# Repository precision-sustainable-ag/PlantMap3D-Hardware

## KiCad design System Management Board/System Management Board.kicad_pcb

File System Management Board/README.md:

The system management board handles all power distribution in the multi-camera system and a few other auxiliary functions. The PCB is designed using KiCad.

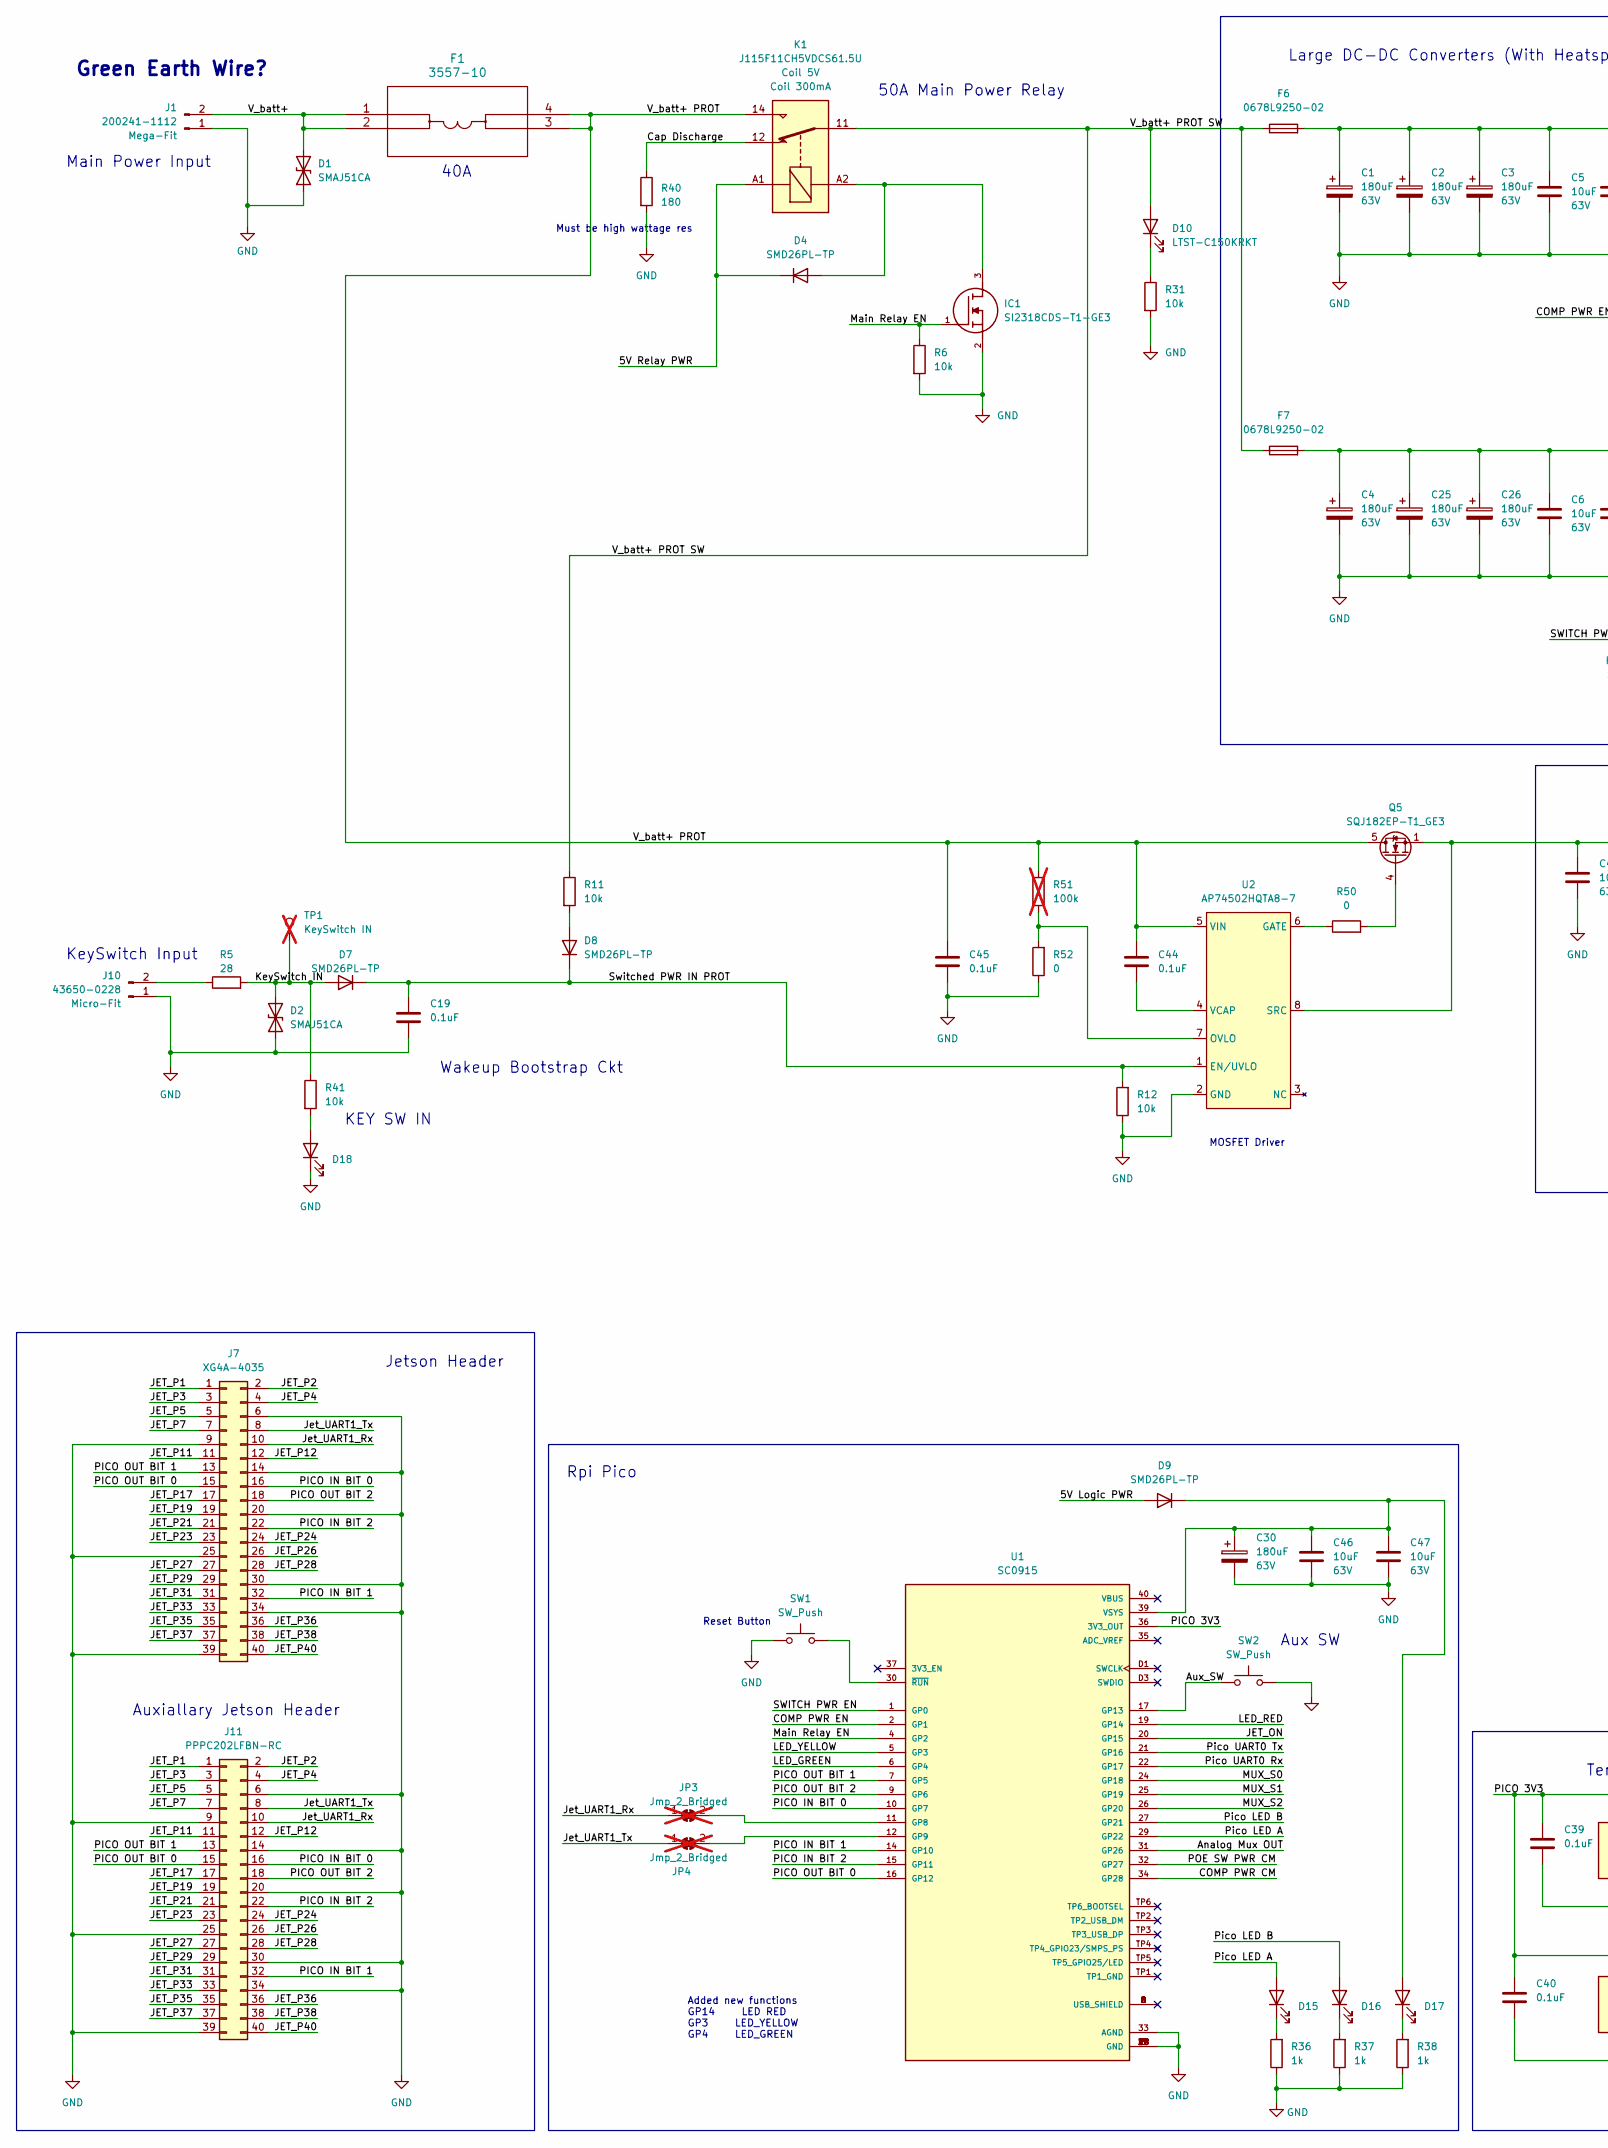
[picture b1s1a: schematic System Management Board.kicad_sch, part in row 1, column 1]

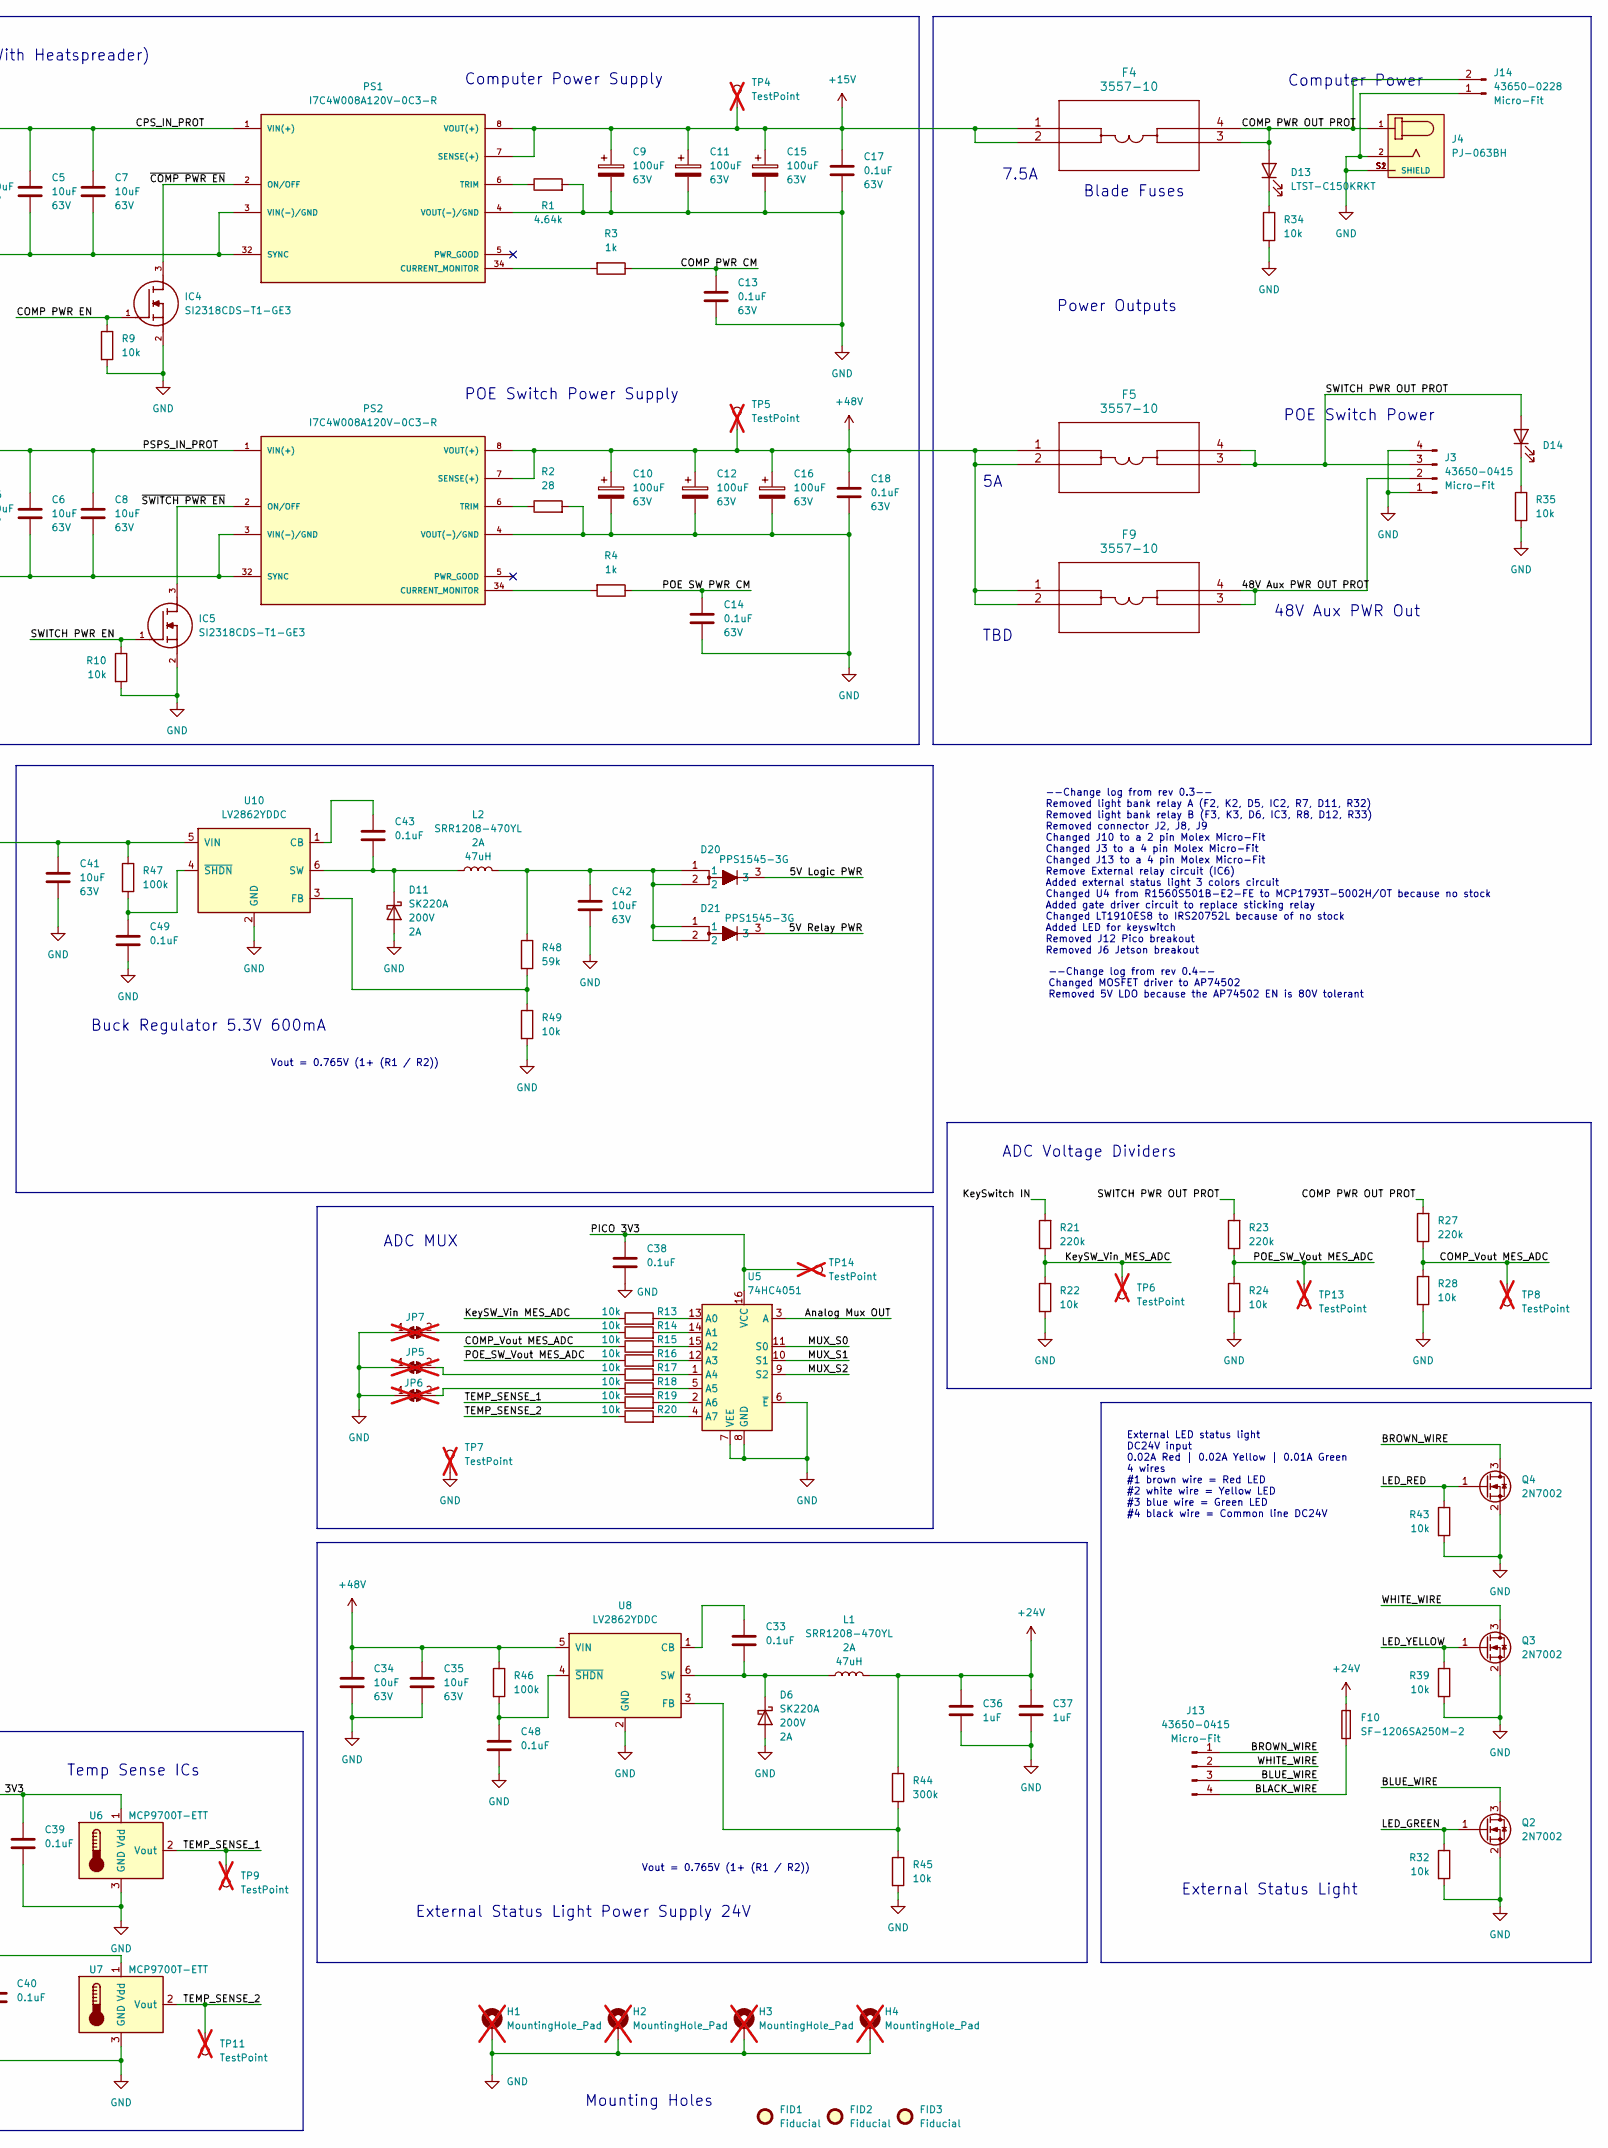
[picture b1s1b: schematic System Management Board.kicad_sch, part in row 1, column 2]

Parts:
C1, C2, C3, C4, C25, C26, C30: 180uF; CP_Elec_10x12.6; Voltage 63V
C5, C6, C7, C8, C34, C35, C41, C42, C46, C47: 10uF; C_1210_3225Metric; Voltage 63V
C9, C10, C11, C12, C15, C16: 100uF; CP_Elec_10x12.6; Voltage 63V
C13, C14, C17, C18, C19, C33, C38, C39, C40, C43, C44, C45, C48, C49: 0.1uF; C_0603_1608Metric; Voltage 63V
C36, C37: 1uF; C_1210_3225Metric
D1, D2: SMAJ51CA; D_SMA
D4, D7, D8, D9: SMD26PL-TP; D_SOD-123F
D6, D11: SK220A; D_SMA; Voltage 200V
D10, D13, D14, D15, D16, D17, D18: LTST-C150KRKT; LED_1206_3216Metric
D20, D21: PPS1545-3G; TO-277B
F1, F4, F5, F9: 3557-10
F6, F7: 0678L9250-02; FUSC9830X318N
F10: SF-1206SA250M-2; Fuse_1206_3216Metric_Pad1.42x1.75mm_HandSolder
FID1, FID2, FID3: Fiducial; Fiducial_1mm_Mask2mm
H1, H2, H3, H4: MountingHole_Pad; MountingHole_3.2mm_M3_Pad_Via; not fitted
IC1, IC4, IC5: SI2318CDS-T1-GE3; SOT-23; MANUFACTURER_PART_NUMBER SI2318CDS-T1-GE3; MOUSER_PART_NUMBER 781-SI2318CDS-T1-GE3
J1: 200241-1112; Molex_Mega-Fit_20024-11112_2x01_P5.70mm_Vertical
J3, J13: 43650-0415; Molex_Micro-Fit_3.0_43650-0415_1x04_P3.00mm_Vertical
J4: PJ-063BH; CUI_PJ-063BH
J7: XG4A-4035; PinHeader_2x20_P2.54mm_Horizontal
J10, J14: 43650-0228; Molex_Micro-Fit_3.0_43650-0215_1x02_P3.00mm_Vertical
J11: PPPC202LFBN-RC; PinHeader_2x20_P2.54mm_Vertical
JP3, JP4: Jmp_2_Bridged; SolderJumper-2_P1.3mm_Bridged_Pad1.0x1.5mm; not fitted
JP5, JP6, JP7: Jmp_2_Bridged; SolderJumper-2_P1.3mm_Bridged_RoundedPad1.0x1.5mm; not fitted
K1: J115F11CH5VDCS61.5U; Relay_SPDT_RAYEX-L90S; Coil Voltage Coil 5V
L1, L2: SRR1208-470YL; L_Bourns_SRR1208_12.7x12.7mm
PS1, PS2: I7C4W008A120V-0C3-R; CONV_I7C4W008A120V-0C3-R
Q2, Q3, Q4: 2N7002; SOT-23
Q5: SQJ182EP-T1_GE3; PowerPAK SO-8L
R1: 4.64k; R_0603_1608Metric
R2, R5: 28; R_1206_3216Metric
R3, R4, R36, R37, R38: 1k; R_0603_1608Metric
R6, R9, R10, R11, R12, R13, R14, R15, R16, R17, R18, R19, R20, R22, R24, R28, R31, R32, R34, R35, R39, R41, R43, R45, R49: 10k; R_0603_1608Metric
R21, R23, R27: 220k; R_0603_1608Metric
R40: 180; RES_3540_TEC; MPN 3540180RJT
R44: 300k; R_0603_1608Metric
R46, R47: 100k; R_0603_1608Metric
R48: 59k; R_0603_1608Metric
R50, R52: 0; R_0603_1608Metric
R51: 100k; R_0603_1608Metric; not fitted
SW1, SW2: SW_Push; SW_SPST_TL3305B
TP1: KeySwitch IN; TestPoint_Pad_D1.0mm; not fitted
TP4, TP5, TP6, TP7, TP8, TP9, TP11, TP13, TP14: TestPoint; TestPoint_Pad_D1.0mm; not fitted
U1: SC0915; MODULE_SCO915_Custom_HeaderStyle; PARTREV 1.6
U2: AP74502HQTA8-7; SOT-23-8
U5: 74HC4051; TSSOP-16_4.4x5mm_P0.65mm
U6, U7: MCP9700T-ETT; SOT-23
U8, U10: LV2862YDDC; SOT-23-6

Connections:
+15V: C9.1, C11.1, C15.1, C17.1, F4.1, F4.2, PS1.7 (SENSE(+)), PS1.8 (VOUT(+)), TP4.1 (1_1)
+24V: C36.1, C37.1, F10.2, L1.2, R44.1
+48V: C10.1, C12.1, C16.1, C18.1, C34.1, C35.1, F5.1, F5.2, F9.1, F9.2, PS2.7 (SENSE(+)), PS2.8 (VOUT(+)), R46.1, TP5.1 (1_1), U8.5 (VIN)
/5V Logic PWR: D9.2 (A), D20.3
/5V Relay PWR: D4.1 (K), D21.3, K1.A1
/48V Aux PWR OUT PROT: F9.3, F9.4, J3.2
/Analog Mux OUT: U1.31 (GP26), U5.3 (A)
/Aux_SW: SW2.1, U1.17 (GP13)
/BLACK_WIRE: F10.1, J13.4
/BLUE_WIRE: J13.3, Q2.3 (D)
/BROWN_WIRE: J13.1, Q4.3 (D)
/COMP PWR CM: C13.1, R3.1, U1.34 (GP28)
/COMP PWR EN: IC4.1, R9.1, U1.2 (GP1)
/COMP PWR OUT PROT: D13.2 (A), F4.3, F4.4, J4.1, J14.2, R27.2
/COMP_Vout MES_ADC: R15.1, R27.1, R28.1, TP8.1 (1_1)
/CPS_IN_PROT: C1.1, C2.1, C3.1, C5.1, C7.1, F6.2, PS1.1 (VIN(+))
/Cap Discharge: K1.12, R40.1
/JET_ON: U1.20 (GP15)
/JET_P1: J7.1, J11.1
/JET_P2: J7.2, J11.2
/JET_P3: J7.3, J11.3
/JET_P4: J7.4, J11.4
/JET_P5: J7.5, J11.5
/JET_P7: J7.7, J11.7
/JET_P11: J7.11, J11.11
/JET_P12: J7.12, J11.12
/JET_P17: J7.17, J11.17
/JET_P19: J7.19, J11.19
/JET_P21: J7.21, J11.21
/JET_P23: J7.23, J11.23
/JET_P24: J7.24, J11.24
/JET_P26: J7.26, J11.26
/JET_P27: J7.27, J11.27
/JET_P28: J7.28, J11.28
/JET_P29: J7.29, J11.29
/JET_P31: J7.31, J11.31
/JET_P33: J7.33, J11.33
/JET_P35: J7.35, J11.35
/JET_P36: J7.36, J11.36
/JET_P37: J7.37, J11.37
/JET_P38: J7.38, J11.38
/JET_P40: J7.40, J11.40
/Jet_UART1_Rx: J7.10, J11.10, JP3.1 (A)
/Jet_UART1_Tx: J7.8, J11.8, JP4.1 (A)
/KeySW_Vin MES_ADC: R13.1, R21.1, R22.1, TP6.1 (1_1)
/KeySwitch IN: D2.2 (A2), D7.2 (A), R5.2, R21.2, R41.1, TP1.1 (1_1)
/LED_GREEN: Q2.1 (G), R32.1, U1.6 (GP4)
/LED_RED: Q4.1 (G), R43.1, U1.19 (GP14)
/LED_YELLOW: Q3.1 (G), R39.1, U1.5 (GP3)
/MUX_S0: U1.24 (GP18), U5.11 (S0)
/MUX_S1: U1.25 (GP19), U5.10 (S1)
/MUX_S2: U1.26 (GP20), U5.9 (S2)
/Main Relay EN: IC1.1, R6.1, U1.4 (GP2)
/PICO 3V3: C38.1, C39.1, C40.1, TP14.1 (1_1), U1.36 (3V3_OUT), U5.16 (VCC), U6.1 (Vdd), U7.1 (Vdd)
/PICO IN BIT 0: J7.16, J11.16, U1.10 (GP7)
/PICO IN BIT 1: J7.32, J11.32, U1.14 (GP10)
/PICO IN BIT 2: J7.22, J11.22, U1.15 (GP11)
/PICO OUT BIT 0: J7.15, J11.15, U1.16 (GP12)
/PICO OUT BIT 1: J7.13, J11.13, U1.7 (GP5)
/PICO OUT BIT 2: J7.18, J11.18, U1.9 (GP6)
/POE SW PWR CM: C14.1, R4.1, U1.32 (GP27)
/POE_SW_Vout MES_ADC: R16.1, R23.1, R24.1, TP13.1 (1_1)
/PSPS_IN_PROT: C4.1, C6.1, C8.1, C25.1, C26.1, F7.2, PS2.1 (VIN(+))
/Pico LED A: D15.2 (A), U1.29 (GP22)
/Pico LED B: D16.2 (A), U1.27 (GP21)
/Pico UART0 Rx: U1.22 (GP17)
/Pico UART0 Tx: U1.21 (GP16)
/SWITCH PWR EN: IC5.1, R10.1, U1.1 (GP0)
/SWITCH PWR OUT PROT: D14.2 (A), F5.3, F5.4, J3.3, R23.2
/Switched PWR IN PROT: C19.1, D7.1 (K), D8.1 (K), R12.2, U2.1 (EN/UVLO)
/TEMP_SENSE_1: R19.1, TP9.1 (1_1), U6.2 (Vout)
/TEMP_SENSE_2: R20.1, TP11.1 (1_1), U7.2 (Vout)
/V_batt+: D1.2 (A2), F1.1, F1.2, J1.2
/V_batt+ PROT: C44.1, C45.1, F1.3, F1.4, K1.14, Q5.5 (D), R51.1, U2.5 (VIN)
/V_batt+ PROT SW: D10.2 (A), F6.1, F7.1, K1.11, R11.1
/WHITE_WIRE: J13.2, Q3.3 (D)
/~COMP PWR EN: IC4.3, PS1.2 (ON/OFF)
/~SWITCH PWR EN: IC5.3, PS2.2 (ON/OFF)
GND: C1.2, C2.2, C3.2, C4.2, C5.2, C6.2, C7.2, C8.2, C9.2, C10.2, C11.2, C12.2, C13.2, C14.2, C15.2, C16.2, C17.2, C18.2, C19.2, C25.2, C26.2, C30.2, C34.2, C35.2, C36.2, C37.2, C38.2, C39.2, C40.2, C41.2, C42.2, C45.2, C46.2, C47.2, C48.2, C49.2, D1.1 (A1), D2.1 (A1), D6.2 (A), D11.2 (A), D18.1 (K), H1.1 (1_1), H2.1 (1_1), H3.1 (1_1), H4.1 (1_1), IC1.2, IC4.2, IC5.2, J1.1, J3.1, J3.4, J4.2, J4.S1 (SHIELD), J4.S2 (SHIELD), J7.6, J7.9, J7.14, J7.20, J7.25, J7.30, J7.34, J7.39, J10.1, J11.6, J11.9, J11.14, J11.20, J11.25, J11.30, J11.34, J11.39, J14.1, JP5.1 (A), JP6.1 (A), JP7.1 (A), PS1.3 (VIN(-)/GND), PS1.4 (VOUT(-)/GND), PS1.32 (SYNC), PS2.3 (VIN(-)/GND), PS2.4 (VOUT(-)/GND), PS2.32 (SYNC), Q2.2 (S), Q3.2 (S), Q4.2 (S), R1.2, R2.2, R6.2, R9.2, R10.2, R12.1, R22.2, R24.2, R28.2, R31.2, R32.2, R34.2, R35.2, R36.1, R37.1, R38.1, R39.2, R40.2, R43.2, R45.2, R49.2, R52.1, SW1.1, SW2.2, TP7.1 (1_1)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
unnamed: C42.1, D20.1, D20.2, D21.1, D21.2, L2.2, R48.1
unnamed: D4.2 (A), IC1.3, K1.A2
unnamed: C33.2, D6.1 (K), L1.1, U8.6 (SW)
unnamed: D8.2 (A), R11.2
unnamed: D10.1 (K), R31.1
unnamed: C43.2, D11.1 (K), L2.1, U10.6 (SW)
unnamed: D13.1 (K), R34.1
unnamed: D14.1 (K), R35.1
unnamed: D15.1 (K), R36.2
unnamed: D16.1 (K), R37.2
unnamed: C30.1, C46.1, C47.1, D9.1 (K), D17.2 (A), U1.39 (VSYS)
unnamed: D17.1 (K), R38.2
unnamed: D18.2 (A), R41.2
unnamed: J10.2, R5.1
unnamed: JP3.2 (B), U1.11 (GP8)
unnamed: JP4.2 (B), U1.12 (GP9)
unnamed: JP5.2 (B), R17.1
unnamed: JP6.2 (B), R18.1
unnamed: JP7.2 (B), R14.1
unnamed: PS1.34 (CURRENT_MONITOR), R3.2
unnamed: PS1.6 (TRIM), R1.1
unnamed: PS2.34 (CURRENT_MONITOR), R4.2
unnamed: PS2.6 (TRIM), R2.1
unnamed: Q5.4 (G), R50.2
unnamed: SW1.2, U1.30 (~RUN)
unnamed: R50.1, U2.6 (GATE)
unnamed: R51.2, R52.2, U2.7 (OVLO)
unnamed: C44.2, U2.4 (VCAP)
unnamed: R13.2, U5.13 (A0)
unnamed: R14.2, U5.14 (A1)
unnamed: R15.2, U5.15 (A2)
unnamed: R16.2, U5.12 (A3)
unnamed: R17.2, U5.1 (A4)
unnamed: R18.2, U5.5 (A5)
unnamed: R19.2, U5.2 (A6)
unnamed: R20.2, U5.4 (A7)
unnamed: C33.1, U8.1 (CB)
unnamed: R44.2, R45.1, U8.3 (FB)
unnamed: C48.1, R46.2, U8.4 (~SHDN)
unnamed: C43.1, U10.1 (CB)
unnamed: R48.2, R49.1, U10.3 (FB)
unnamed: C41.1, Q5.1 (S), Q5.2 (S), Q5.3 (S), R47.1, U2.8 (SRC), U10.5 (VIN)
unnamed: C49.1, R47.2, U10.4 (~SHDN)

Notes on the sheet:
KeySwitch Input
TBD
48V Aux PWR Out
Power Outputs
Buck Regulator 5.3V 600mA
Auxiallary Jetson Header
40A
Green Earth Wire?
MOSFET Driver
50A Main Power Relay
--Change log from rev 0.4-- Changed MOSFET driver to AP74502 Removed 5V LDO because the AP74502 EN is 80V tolerant
External LED status light DC24V input 0.02A Red | 0.02A Yellow | 0.01A Green 4 wires #1 brown wire = Red LED #2 white wire = Yellow LED #3 blue wire = Green LED #4 black wire = Common line DC24V
Computer Power
Large DC-DC Converters (With Heatspreader)
Computer Power Supply
Vout = 0.765V (1+ (R1 / R2))
Main Power Input
Blade Fuses
Added new functions GP14 LED RED GP3 LED_YELLOW GP4 LED_GREEN
POE Switch Power Supply
KEY SW IN
Rpi Pico
Must be high wattage res
Temp Sense ICs
POE Switch Power
7.5A
--Change log from rev 0.3-- Removed light bank relay A (F2, K2, D5, IC2, R7, D11, R32) Removed light bank relay B (F3, K3, D6, IC3, R8, D12, R33) Removed connector J2, J8, J9 Changed J10 to a 2 pin Molex Micro-Fit Changed J3 to a 4 pin Molex Micro-Fit Changed J13 to a 4 pin Molex Micro-Fit Remove E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
External Status Light Power Supply 24V
ADC Voltage Dividers
Jetson Header
Wakeup Bootstrap Ckt
Mounting Holes
ADC MUX
Aux SW
Reset Button
External Status Light

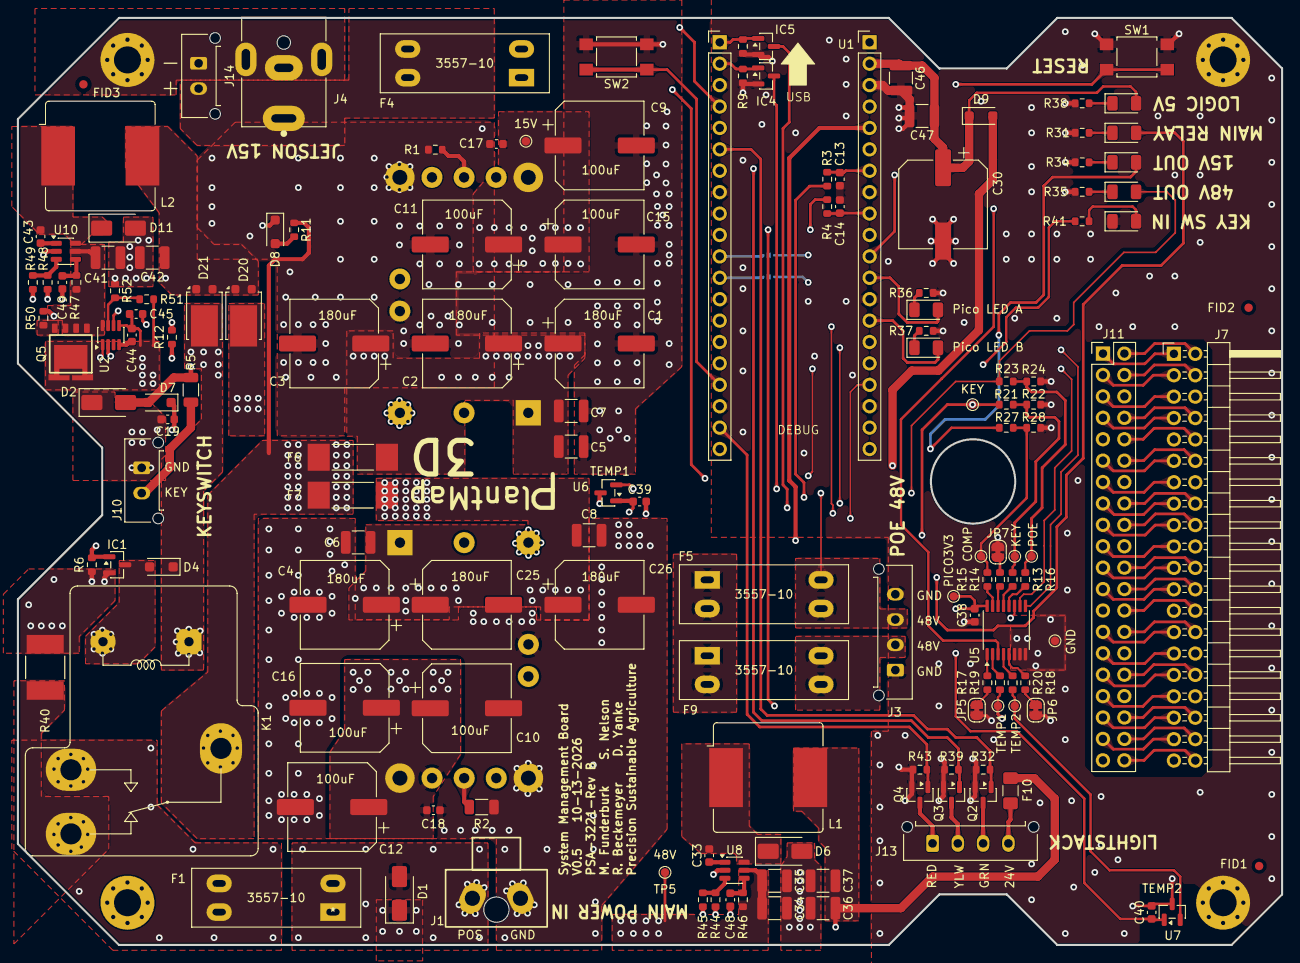
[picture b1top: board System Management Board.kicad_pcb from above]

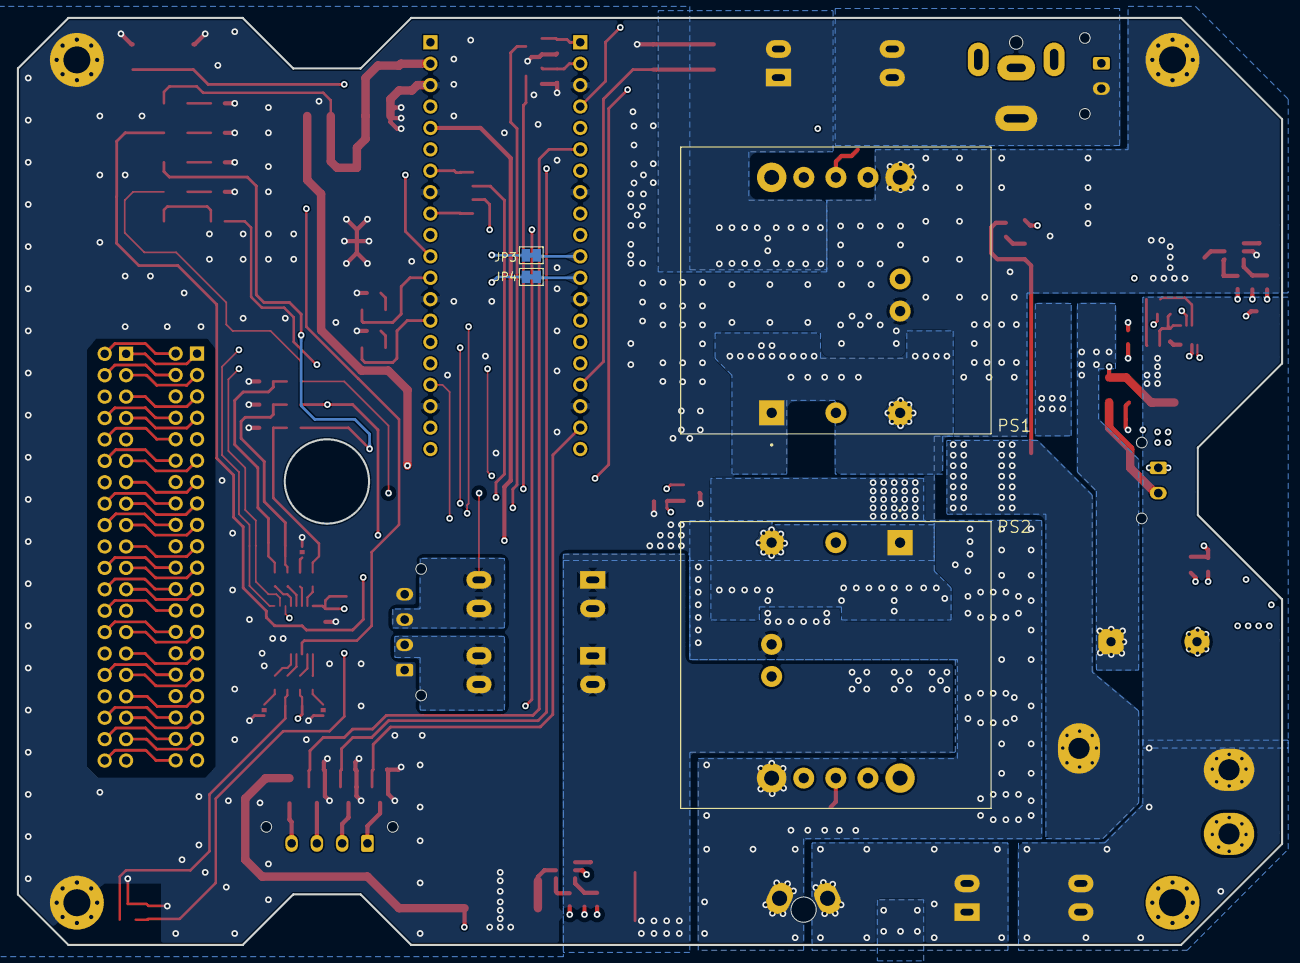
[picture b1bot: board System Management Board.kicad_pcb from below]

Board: 4 copper layers, 150.0 x 110.0 mm, 158 parts (4 on the bottom side), 119 nets.

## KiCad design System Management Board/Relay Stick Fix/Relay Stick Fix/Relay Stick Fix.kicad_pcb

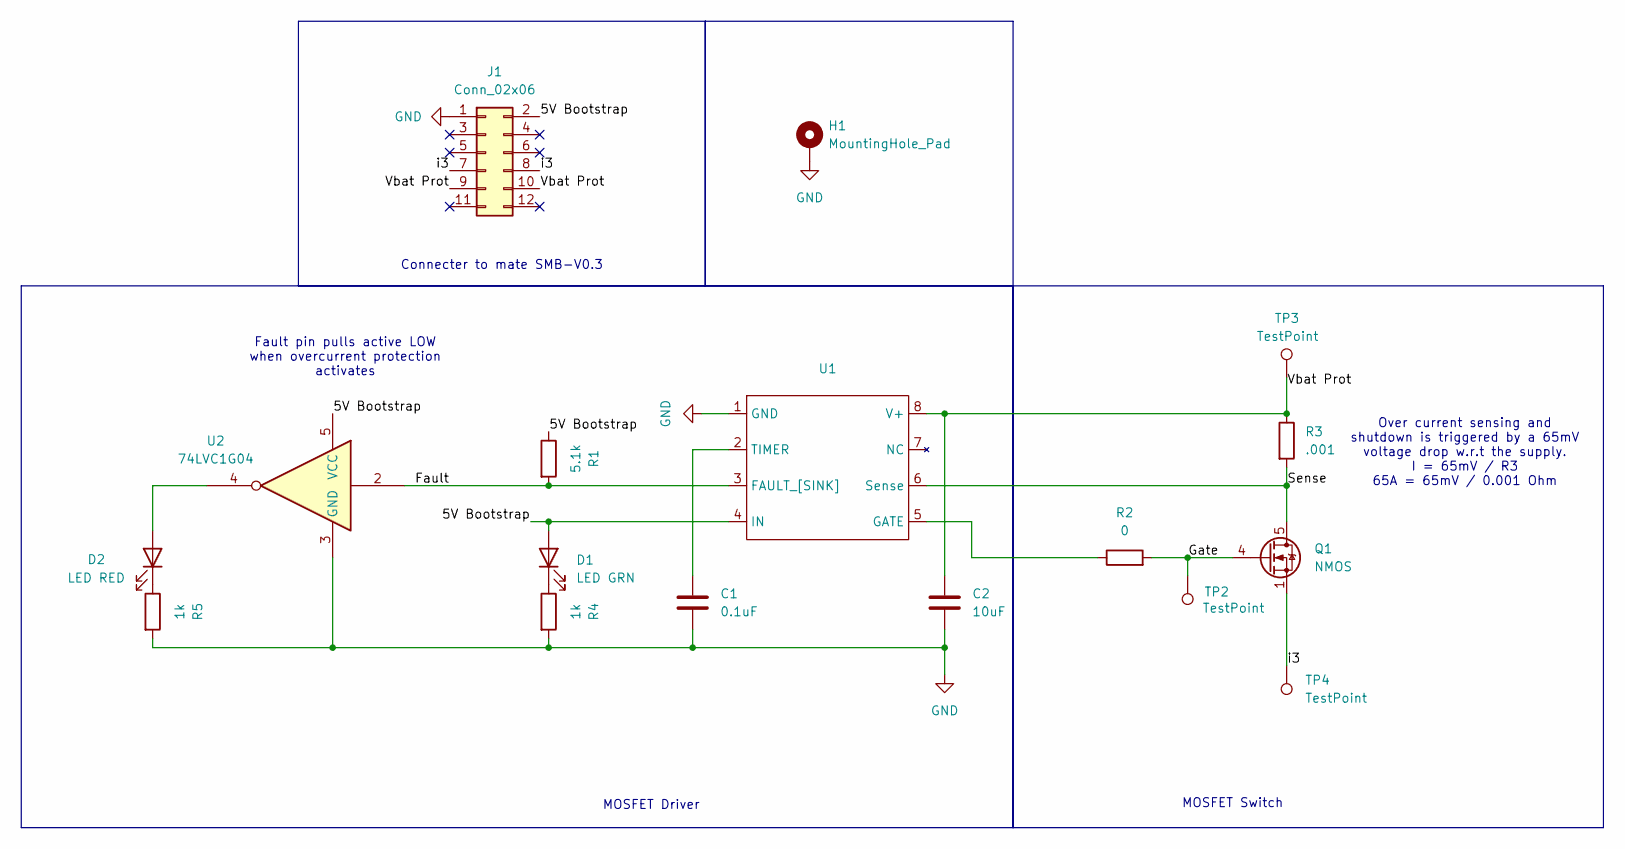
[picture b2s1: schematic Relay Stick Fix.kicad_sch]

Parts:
C1: 0.1uF; C_1206_3216Metric_Pad1.33x1.80mm_HandSolder
C2: 10uF; C_1210_3225Metric_Pad1.33x2.70mm_HandSolder
D1: LED GRN; LED_1206_3216Metric_Pad1.42x1.75mm_HandSolder
D2: LED RED; LED_1206_3216Metric_Pad1.42x1.75mm_HandSolder
H1: MountingHole_Pad; MountingHole_3.2mm_M3_DIN965_Pad
J1: Conn_02x06; PinHeader_2x06_P2.54mm_Vertical_SMD
Q1: NMOS; PowerPAK_SO-8L_Single
R1: 5.1k; R_1206_3216Metric_Pad1.30x1.75mm_HandSolder
R2: 0; R_1206_3216Metric_Pad1.30x1.75mm_HandSolder
R3: .001; R_2512_6332Metric
R4, R5: 1k; R_1206_3216Metric_Pad1.30x1.75mm_HandSolder
TP2: TestPoint; TestPoint_Pad_D1.0mm
TP3, TP4: TestPoint; TestPoint_THTPad_D1.0mm_Drill0.5mm
U1: SOIC-8-1EP_3.9x4.9mm_P1.27mm_EP2.29x3mm
U2: 74LVC1G04; SOT-23-5

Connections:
/5V Bootstrap: D1.2 (A), J1.2, R1.1, U1.4 (IN), U2.5 (VCC)
/Fault: R1.2, U1.3 (FAULT_[SINK]), U2.2
/Gate: Q1.4 (G), R2.2, TP2.1
/Sense: Q1.5 (D), R3.2, U1.6 (Sense)
/Vbat Prot: C2.1, J1.9, J1.10, R3.1, TP3.1, U1.8 (V+)
/i3: J1.7, J1.8, Q1.1 (S), Q1.2 (S), Q1.3 (S), TP4.1
GND: C1.2, C2.2, H1.1, J1.1, R4.2, R5.2, U1.1 (GND), U2.3 (GND)
unnamed: D1.1 (K), R4.1
unnamed: D2.2 (A), U2.4
unnamed: D2.1 (K), R5.1
unnamed: R2.1, U1.5 (GATE)
unnamed: C1.1, U1.2 (TIMER)

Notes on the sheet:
MOSFET Switch
Connecter to mate SMB-V0.3
Over current sensing and shutdown is triggered by a 65mV voltage drop w.r.t the supply. I = 65mV / R3 65A = 65mV / 0.001 Ohm
Fault pin pulls active LOW when overcurrent protection activates
MOSFET Driver

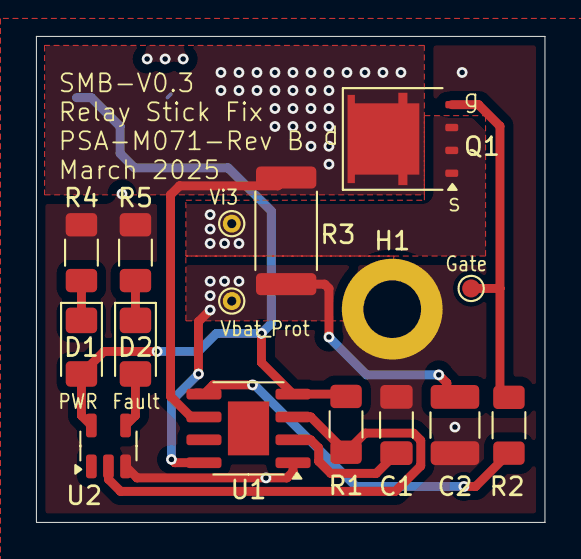
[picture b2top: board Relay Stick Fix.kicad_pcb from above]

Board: 4 copper layers, 28.2 x 27.0 mm, 17 parts (1 on the bottom side), 12 nets.

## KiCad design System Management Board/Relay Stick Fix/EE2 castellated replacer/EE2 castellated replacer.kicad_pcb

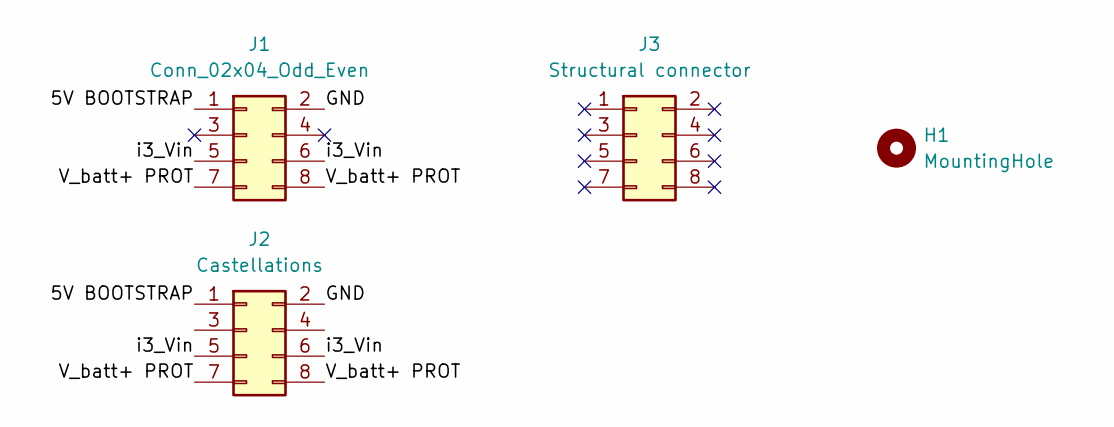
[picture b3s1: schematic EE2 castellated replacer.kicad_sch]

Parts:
H1: MountingHole; MountingHole_3.2mm_M3_DIN965_Pad
J1: Conn_02x04_Odd_Even; PinSocket_2x04_P2.54mm_Vertical_SMD
J2: Castellations; EE2-5NU Castellated
J3: Structural connector; PinSocket_2x04_P2.54mm_Vertical_SMD

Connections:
/5V BOOTSTRAP: J1.1, J2.1
/GND: J1.2, J2.2
/V_batt+ PROT: J1.7, J1.8, J2.7, J2.8
/i3_Vin: J1.5, J1.6, J2.5, J2.6

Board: 2 copper layers, 4 parts (0 on the bottom side), 4 nets, no tracks yet.

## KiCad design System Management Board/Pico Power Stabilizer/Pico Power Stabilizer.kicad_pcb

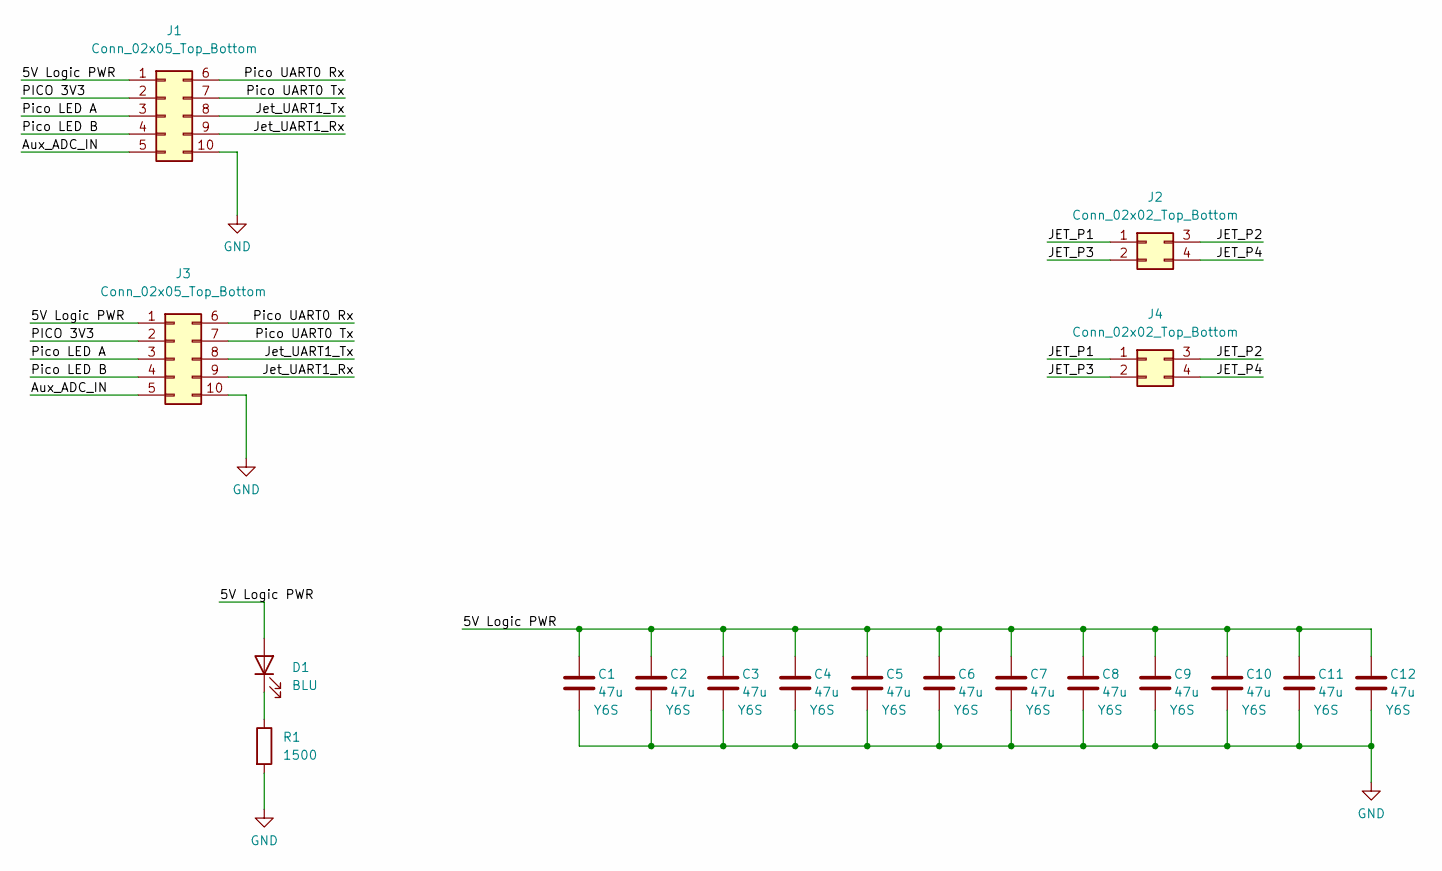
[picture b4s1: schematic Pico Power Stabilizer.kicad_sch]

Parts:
C1, C2, C3, C4, C5, C6, C7, C8, C9, C10, C11, C12: 47u; C_1210_3225Metric
D1: BLU; LED_0603_1608Metric
J1: Conn_02x05_Top_Bottom; PinHeader_2x05_P2.54mm_Vertical_SMD
J2: Conn_02x02_Top_Bottom; PinHeader_2x02_P2.54mm_Vertical_SMD
J3: Conn_02x05_Top_Bottom; PinSocket_2x05_P2.54mm_Vertical_SMD
J4: Conn_02x02_Top_Bottom; PinSocket_2x02_P2.54mm_Vertical_SMD
R1: 1500; R_0603_1608Metric

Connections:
/5V Logic PWR: C1.1, C2.1, C3.1, C4.1, C5.1, C6.1, C7.1, C8.1, C9.1, C10.1, C11.1, C12.1, D1.2 (A), J1.1, J3.1
/Aux_ADC_IN: J1.5, J3.5
/JET_P1: J2.1, J4.1
/JET_P2: J2.3, J4.3
/JET_P3: J2.2, J4.2
/JET_P4: J2.4, J4.4
/Jet_UART1_Rx: J1.9, J3.9
/Jet_UART1_Tx: J1.8, J3.8
/PICO 3V3: J1.2, J3.2
/Pico LED A: J1.3, J3.3
/Pico LED B: J1.4, J3.4
/Pico UART0 Rx: J1.6, J3.6
/Pico UART0 Tx: J1.7, J3.7
GND: C1.2, C2.2, C3.2, C4.2, C5.2, C6.2, C7.2, C8.2, C9.2, C10.2, C11.2, C12.2, J1.10, J3.10, R1.2
unnamed: D1.1 (K), R1.1

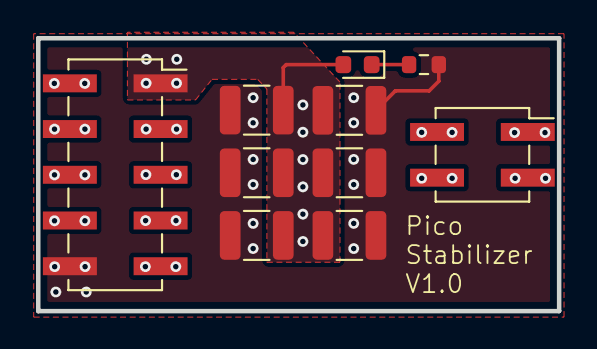
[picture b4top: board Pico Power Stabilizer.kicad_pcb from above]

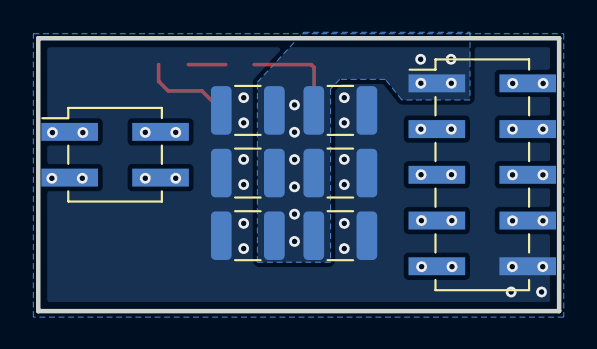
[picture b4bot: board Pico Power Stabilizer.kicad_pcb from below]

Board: 2 copper layers, 28.9 x 15.2 mm, 18 parts (8 on the bottom side), 15 nets.

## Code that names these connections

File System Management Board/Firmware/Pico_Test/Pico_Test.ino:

#define IN0 7
#define IN1 10
#define IN2 11
#define OUT0 12
#define OUT1 27
#define OUT2 28
#define LEDA 22
#define LEDB 21
#define SWITCH_PWR_EN 0
#define COMP_PWR_EN 1
#define MAIN_RELAY 2
#define LIGHT_A 3
#define LIGHT_B 4
#define MUX_S2 20
#define MUX_S1 19
#define MUX_S0 18
#define ADC_MUX 26
#define JET_ON 15

int COMP_PWR_STATE = 0;
int SWITCH_PWR_STATE = 0;
int MAIN_RELAY_STATE = 0;
int LEDA_STATE = 0;
int LEDB_STATE = 0;
int LIGHT_A_STATE = 0;
int LIGHT_B_STATE = 0;
int JET_ON_STATE = 0;

//The threshold for deciding if power is on
//If voltage reading it greater, it is on, if less, off. 
int threshold = 100;

bool American = false; 

//Since there are several 3-bit interfaces, a dedicated structure
//seemed useful. 
struct bits{
  int S2,S1,S0;
};

struct bits AUX_Voltage = {0,0,1};
struct bits Temp_Sensor1 = {1,1,0};
struct bits Temp_Sensor2 = {1,1,1};

void set_mux(struct bits pins){
  delay(10);
  digitalWrite(MUX_S2,pins.S2);
  digitalWrite(MUX_S1,pins.S1);
  digitalWrite(MUX_S0,pins.S0);
  delay(10);
}

int read_ADC_MUX(struct bits pins){
  set_mux(pins);
  int data = analogRead(ADC_MUX);
  //set_mux({0,0,0});
  return data;
}

float convt_temp(float temp){
  //The MCP9700T is supposed to have temp coeff Vc = 10mV/˚C and V(0˚) = 400mv. 
  //The datasheet gives the output equation Vout = Va*Vc+V(0˚), where Va = 
  //the ambient temperature. 
  //4096 is based on the RPi Pico's 12-bit ADC readings
  float Vc = 10.0/1000.0;
  float V0 = 400.0/1000.0;
  temp = temp*(5.0/4096.0);
  temp = temp-V0;
  temp = temp/Vc;
  if (American){
    //Fahrenheit conversion
    temp = (temp*1.8)+32.0;
  }
  return temp;
}

float check_temp(int sensor){
  struct bits temp_mux1 = {1,1,0};
  struct bits temp_mux2 = {1,1,1};
  float temp = 0.0;
  if (sensor == 1){
    temp = (float)read_ADC_MUX(temp_mux1);
  }
  else if (sensor == 2){
    temp = (float)read_ADC_MUX(temp_mux2);
  }
  temp = convt_temp(temp);
  return temp;
}

void toggle(int pin_to_toggle, bool state){
  digitalWrite(pin_to_toggle,!state);
}

void parser(String input_string){
  int input_char = (int)input_string[0];
  switch (input_char) {
    //"M" toggles the main relay
    case 77:
      MAIN_RELAY_STATE = !MAIN_RELAY_STATE;
      digitalWrite(MAIN_RELAY,MAIN_RELAY_STATE);
    break;
    case 83:
      //"S" toggles the switch relay
      SWITCH_PWR_STATE = !SWITCH_PWR_STATE;
      digitalWrite(SWITCH_PWR_EN,SWITCH_PWR_STATE);
    break;
    //"C" toggles the computer relay
    case 67:
      COMP_PWR_STATE = !COMP_PWR_STATE;
      digitalWrite(COMP_PWR_EN,COMP_PWR_STATE);
    break;
    //"J" toggles the Jetson on pin
    case 74:
      JET_ON_STATE = !JET_ON_STATE;
      digitalWrite(JET_ON,JET_ON_STATE);
    break;
    //"T" prints temperatures over serial
    case 84:
      Serial.println(check_temp(1));
      Serial.println(check_temp(2));
    break;
    //"a" toggles LEDA
    case 97:
      LEDA_STATE = !LEDA_STATE;
      digitalWrite(LEDA,LEDA_STATE);
    break;
    //"b" toggles LEDB
    case 98:
      LEDB_STATE = !LEDB_STATE;
      digitalWrite(LEDB,LEDB_STATE);
    break;
    //"A" toggles LIGHT_A
    case 65:
      LIGHT_A_STATE = !LIGHT_A_STATE;
      digitalWrite(LIGHT_A,LIGHT_A_STATE);
    break;
    //"B" toggles LIGHT_B
    case 66:
      LIGHT_B_STATE = !LIGHT_B_STATE;
      digitalWrite(LIGHT_B,LIGHT_B_STATE);
    break;
    //"O" enables output pin control parsing expects 4 chars like "O001" MSB (2) to LSB (0)
    case 79:
      digitalWrite(OUT0,((int)input_string[3])-48);
      digitalWrite(OUT1,((int)input_string[2])-48);
      digitalWrite(OUT2,((int)input_string[1])-48);
    break;
    //"I" enables input pin value reading
    case 73:{
      String holder = "";
      holder.concat(digitalRead(IN2));
      holder.concat(digitalRead(IN1));
      holder.concat(digitalRead(IN0));
      Serial.println(holder);
    }
    break;
    //"K" runs shutdown procedure
    case 75:
      shutdown();
    break;
    //"V" reads voltage of input from ADC mux
    case 86:
    {
      struct bits mux_selector = {0,0,1};
      int voltage = read_ADC_MUX(mux_selector);
      Serial.println(voltage);
    }
  }
  Serial.print((char)input_char);
  Serial.print(" ");
  Serial.println("Done");
}

void check_pow(){
  struct bits mux_selector = {0,0,1};
  int voltage = read_ADC_MUX(mux_selector);
  if (voltage >= threshold){
    digitalWrite(SWITCH_PWR_EN,1);
    delay(50);
    digitalWrite(COMP_PWR_EN,1);
  }
  else {
    shutdown();
  }
}

void shutdown(){
  pinMode(JET_ON,OUTPUT);
  digitalWrite(JET_ON,1);
  delay(1000);
  digitalWrite(JET_ON,0);
  //Wait before cutting power
  delay(30000);
  digitalWrite(SWITCH_PWR_EN,0);
  delay(50);
  digitalWrite(COMP_PWR_EN,0);
  delay(50);
  digitalWrite(LIGHT_A,0);
  delay(50);
  digitalWrite(LIGHT_B,0);
  delay(200);
  digitalWrite(MAIN_RELAY,0);
  //End of code
}

void setup() {
  // put your setup code here, to run once:
  pinMode(IN0, INPUT);
  pinMode(IN1, INPUT);
  pinMode(IN2, INPUT);
  pinMode(OUT0, OUTPUT);
  digitalWrite(OUT0,0);
  pinMode(OUT1, OUTPUT);
  digitalWrite(OUT1,0);
  pinMode(OUT2, OUTPUT);
  digitalWrite(OUT2,0);
  pinMode(LIGHT_A,OUTPUT);
  digitalWrite(LIGHT_A,0);
  pinMode(LIGHT_B,OUTPUT);
  digitalWrite(LIGHT_B,0);
  pinMode(LEDA, OUTPUT);
  digitalWrite(LEDA,0);
  pinMode(LEDB, OUTPUT);
  digitalWrite(LEDB,0);
  pinMode(MAIN_RELAY, OUTPUT);
  digitalWrite(MAIN_RELAY,0);
  pinMode(SWITCH_PWR_EN, OUTPUT);
  digitalWrite(SWITCH_PWR_EN,0);
  pinMode(COMP_PWR_EN, OUTPUT);
  digitalWrite(COMP_PWR_EN, 0);
  Serial.begin(115200);
  for (int i = 0; i<10;i++){
    delay(1000);
    if (Serial.available()>0){
      String data = Serial.readStringUntil(10);
      data.trim();
      parser(data);
    }
  }
  digitalWrite(MAIN_RELAY,1);
  //Pi is in control
  for (int i = 0; i<10;i++){
    delay(1000);
    if (Serial.available()>0){
      String data = Serial.readStringUntil(10);
      data.trim();
      parser(data);
    }
  }
  //check_pow();
}

void loop() {
  // put your main code here, to run repeatedly:
  //Analog read is rather inefficient timewise, so only check power once every
  //5 seconds. 
  if ((millis() % 5000) <= 50){
    struct bits input_bits;
    input_bits = {digitalRead(IN0),digitalRead(IN1),digitalRead(IN2)};
    //Input 11* Light A, 1*1 Light B, 01* LED A, 0*1 LED B
    digitalWrite(input_bits.S0 && input_bits.S1, LIGHT_A);
    digitalWrite(input_bits.S0 && input_bits.S2, LIGHT_B);
    digitalWrite(!input_bits.S0&&input_bits.S1,LEDA);
    digitalWrite(!input_bits.S0&&input_bits.S2,LEDB);
    struct bits mux_selector;
    mux_selector = {0,0,1};
    int voltage = read_ADC_MUX(mux_selector);
    delay(100);
    if (voltage < threshold){
      //shutdown();
    }
  }
  if (Serial.available()>0){
    String data = Serial.readStringUntil(10);
    data.trim();
    parser(data); 
  }
}

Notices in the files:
parts and their libraries:
Copyright 2021 Accelerated Designs. All rights reserved.
